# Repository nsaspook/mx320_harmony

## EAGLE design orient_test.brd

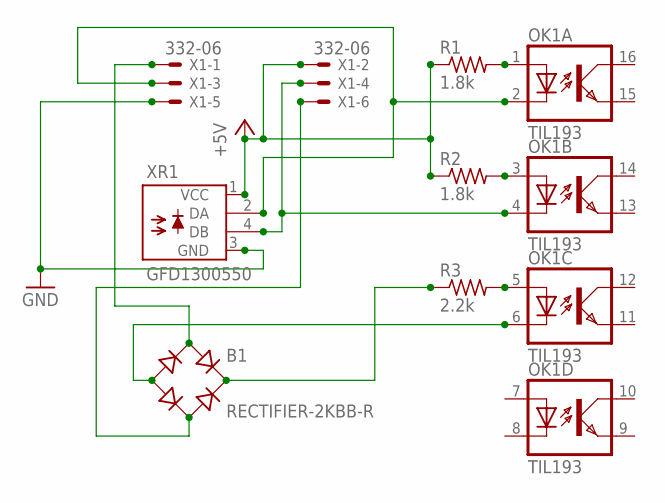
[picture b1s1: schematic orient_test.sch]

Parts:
B1: RECTIFIER-2KBB-R; 2KBB-R
OK1: TIL193; DIL16
R1, R2: 1.8k; 0204V
R3: 2.2k; 0204V
X1: 332-06
XR1: GFD1300550; GFD1300

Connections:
+5V: R1.1, R2.1, X1.2, XR1.1 (VCC)
GND: X1.5, XR1.3 (GND)
unnamed: OK1.1 (A), R1.2
unnamed: OK1.3 (A), R2.2
unnamed: OK1.5 (A), R3.2
unnamed: OK1.2 (C), X1.3, XR1.2 (DA)
unnamed: OK1.4 (C), X1.4, XR1.4 (DB)
unnamed: B1.+, R3.1
unnamed: B1.-, OK1.6 (C)
unnamed: B1.AC1, X1.1
unnamed: B1.AC2, X1.6

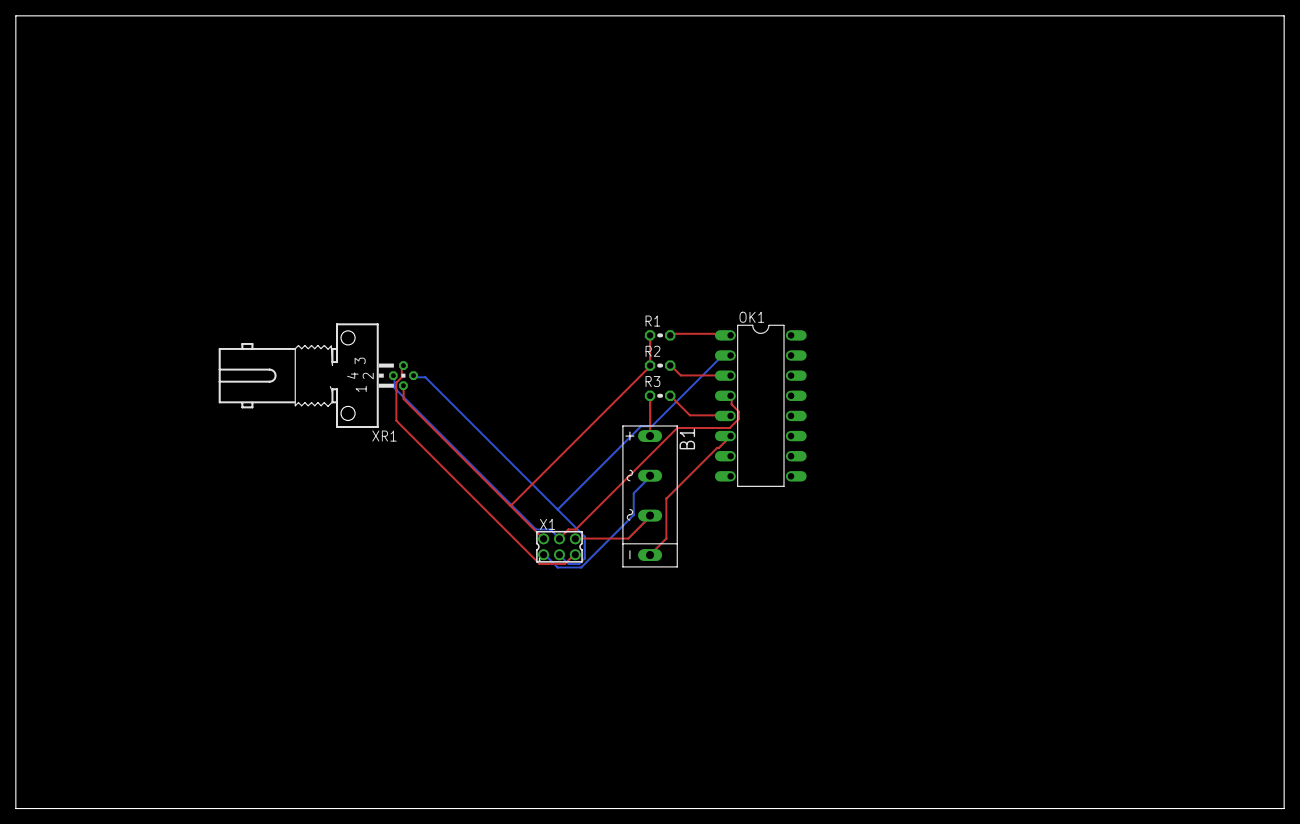
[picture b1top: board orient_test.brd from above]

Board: 2 copper layers, 160.0 x 100.0 mm, 7 parts (0 on the bottom side), 11 nets.

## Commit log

2017-05-09 display updates
2017-08-16 update source
2017-08-18 2.04 update
